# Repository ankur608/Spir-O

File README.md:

# Spir-O
## Open-Source Spirometry for ALL.

### Paper https://doi.org/10.17605/OSF.IO/A82D7

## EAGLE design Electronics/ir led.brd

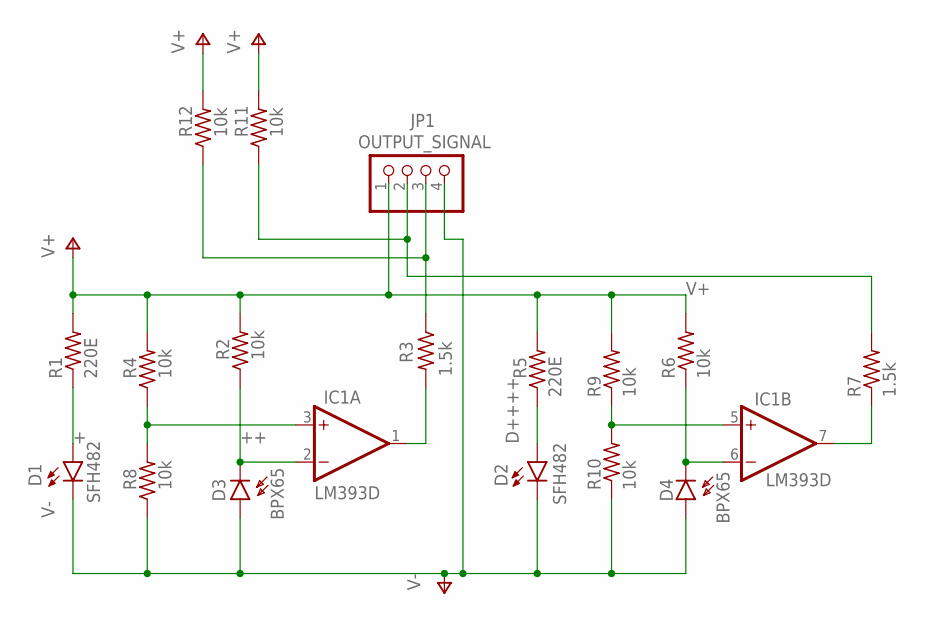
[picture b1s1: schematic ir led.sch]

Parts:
D1, D2: SFH482
D3, D4: BPX65
IC1: LM393D; SO08
JP1: OUTPUT_SIGNAL; 1X04
R1, R5: 220E; 0204/7
R2, R4, R6, R8, R9, R10, R11, R12: 10k; 0204/7
R3, R7: 1.5k; 0204/7

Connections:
+: D1.A, R1.1
++: D3.K (C), IC1.2 (-IN), R2.1
D++++: D2.A, R5.1
unnamed: IC1.3 (+IN), R4.1, R8.2
unnamed: IC1.5 (+IN), R9.1, R10.2
unnamed: IC1.1 (OUT), R3.2
unnamed: IC1.7 (OUT), R7.1
unnamed: D4.K (C), IC1.6 (-IN), R6.1
unnamed: JP1.3, R3.1, R12.1
unnamed: JP1.2, R7.2, R11.1
V+: IC1.8 (V+), JP1.1, R1.2, R2.2, R4.2, R5.2, R6.2, R9.2, R11.2, R12.2
V-: D1.K (C), D2.K (C), D3.A, D4.A, IC1.4 (V-), JP1.4, R8.1, R10.1

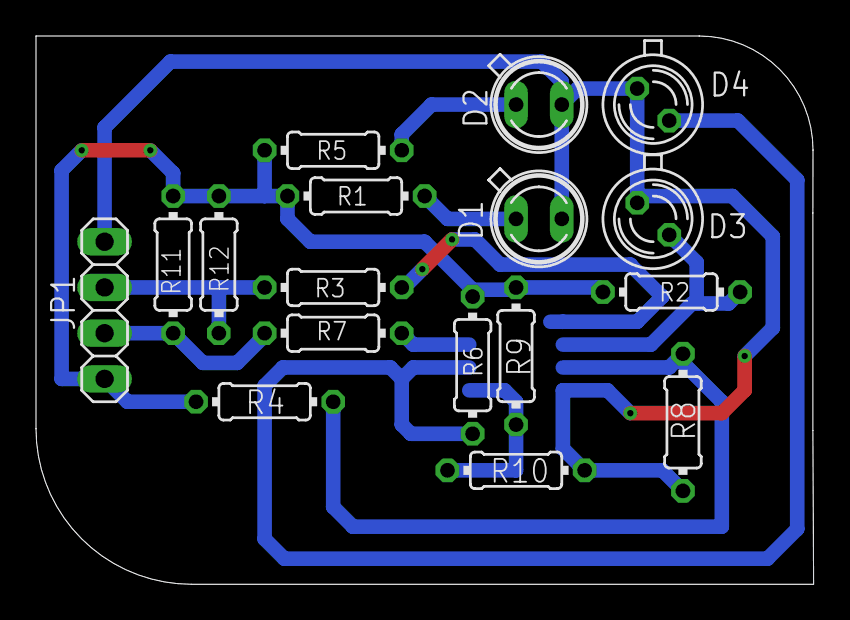
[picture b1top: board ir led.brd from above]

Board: 2 copper layers, 43.2 x 30.5 mm, 18 parts (1 on the bottom side), 12 nets.

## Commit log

2023-02-24 Create LICENSE
2023-02-24 Update LICENSE
